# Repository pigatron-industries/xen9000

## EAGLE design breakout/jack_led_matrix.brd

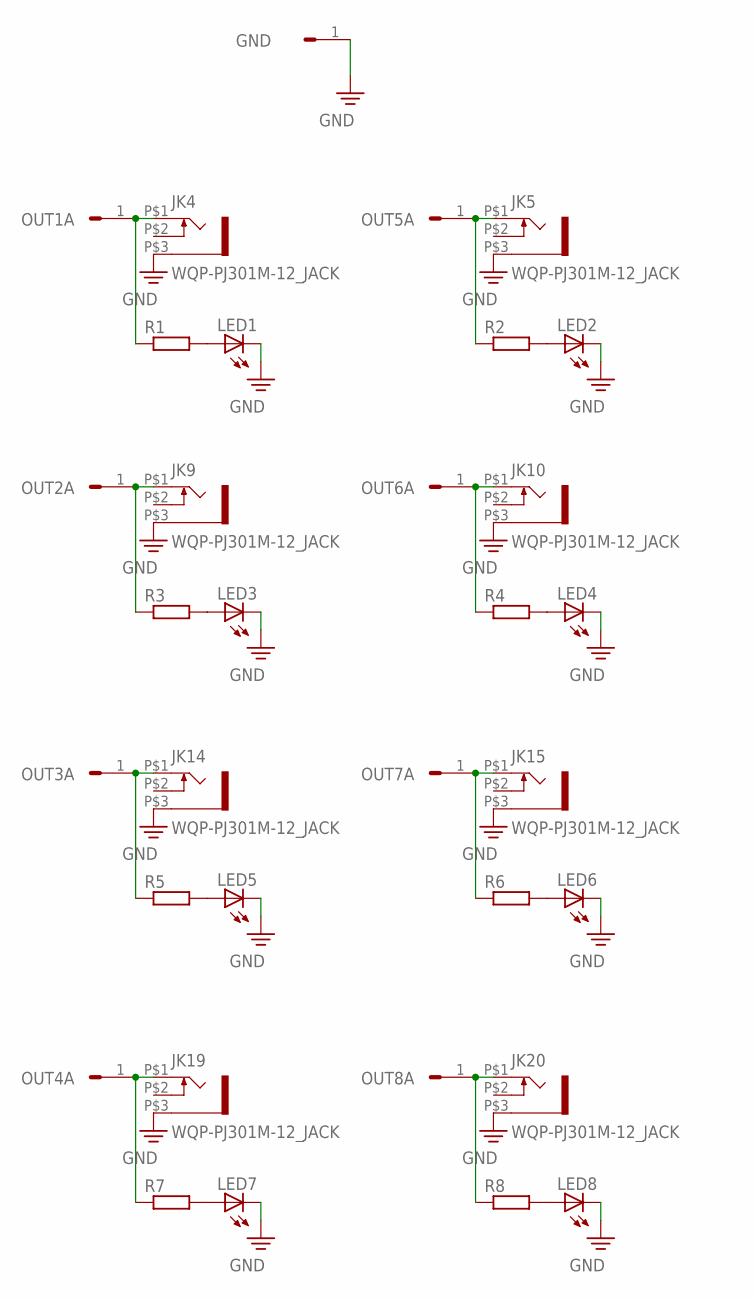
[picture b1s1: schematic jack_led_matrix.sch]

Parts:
GND: HEADER/MALE/01
JK4, JK5, JK9, JK10, JK14, JK15, JK19, JK20: WQP-PJ301M-12_JACK
LED1, LED2, LED3, LED4, LED5, LED6, LED7, LED8: LED3MM
OUT1A, OUT2A, OUT3A, OUT4A, OUT5A, OUT6A, OUT7A, OUT8A: HEADER/MALE/01
R1, R2, R3, R4, R5, R6, R7, R8: RESISTORRESISTOR/UPRIGHT/7.5; RESISTOR/7.5

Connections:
unnamed: JK4.P$1 (2), OUT1A.1, R1.1
unnamed: JK9.P$1 (2), OUT2A.1, R3.1
unnamed: JK14.P$1 (2), OUT3A.1, R5.1
unnamed: JK19.P$1 (2), OUT4A.1, R7.1
unnamed: JK5.P$1 (2), OUT5A.1, R2.1
unnamed: JK10.P$1 (2), OUT6A.1, R4.1
unnamed: JK15.P$1 (2), OUT7A.1, R6.1
unnamed: JK20.P$1 (2), OUT8A.1, R8.1
unnamed: LED1.A, R1.2
unnamed: LED2.A, R2.2
unnamed: LED3.A, R3.2
unnamed: LED4.A, R4.2
unnamed: LED5.A, R5.2
unnamed: LED6.A, R6.2
unnamed: LED7.A, R7.2
unnamed: LED8.A, R8.2
PE: GND.1, JK4.P$3 (1), JK5.P$3 (1), JK9.P$3 (1), JK10.P$3 (1), JK14.P$3 (1), JK15.P$3 (1), JK19.P$3 (1), JK20.P$3 (1), LED1.K (C), LED2.K (C), LED3.K (C), LED4.K (C), LED5.K (C), LED6.K (C), LED7.K (C), LED8.K (C)

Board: 2 copper layers, 33 parts (0 on the bottom side), 17 nets, no tracks yet.

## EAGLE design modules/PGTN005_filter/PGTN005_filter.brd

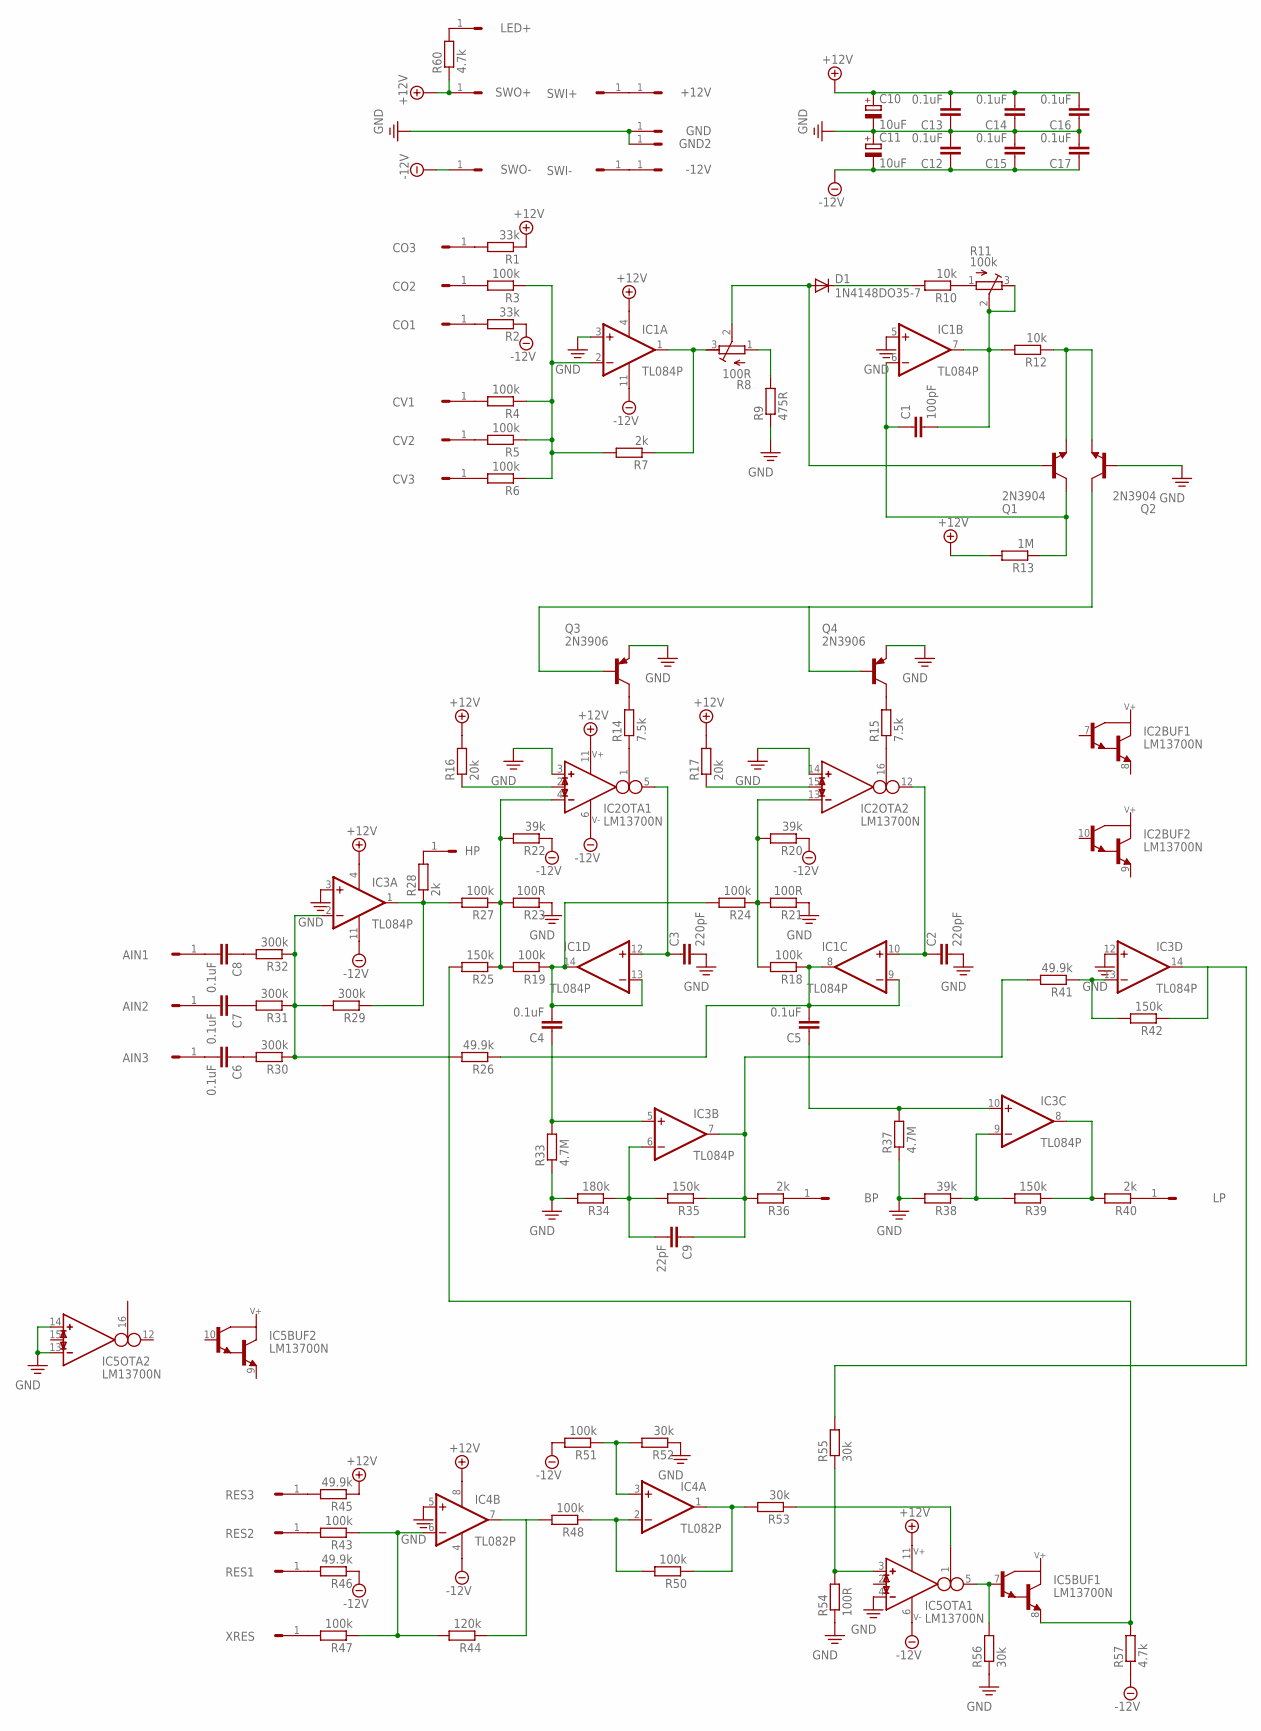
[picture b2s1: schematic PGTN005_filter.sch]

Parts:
+12V: HEADER/MALE/01
-12V: HEADER/MALE/01
AIN1, AIN2, AIN3: HEADER/MALE/01
BP: HEADER/MALE/01
C1: 100pF; CERAMICDISC/5
C2, C3: 220pF; CERAMICDISC/5
C4, C5, C6, C7, C8, C12, C13, C14, C15, C16, C17: 0.1uF; CERAMICDISC/5
C9: 22pF; CERAMICDISC/5
C10, C11: 10uF; E2,5-6
CO1, CO2, CO3: HEADER/MALE/01
CV1, CV2, CV3: HEADER/MALE/01
D1: 1N4148DO35-7; DO35-7
GND, GND2: HEADER/MALE/01
HP: HEADER/MALE/01
IC1, IC3: TL084P; DIL14
IC2, IC5: LM13700N; DIL16
IC4: TL082P; DIL08
LED+: HEADER/MALE/01
LP: HEADER/MALE/01
Q1, Q2: 2N3904; TO92
Q3, Q4: 2N3906; TO92
R1, R2: 33k; RESISTOR/7.5
R3, R4, R5, R6, R18, R19, R24, R27, R43, R47, R48, R50, R51: 100k; RESISTOR/7.5
R7, R28, R36, R40: 2k; RESISTOR/7.5
R8: 100R; TRIMMER/64B
R9: 475R; RESISTOR/7.5
R10, R12: 10k; RESISTOR/7.5
R11: 100k; TRIMMER/64B
R13: 1M; RESISTOR/7.5
R14, R15: 7.5k; RESISTOR/7.5
R16, R17: 20k; RESISTOR/7.5
R20, R22, R38: 39k; RESISTOR/7.5
R21, R23, R54: 100R; RESISTOR/7.5
R25, R35, R39, R42: 150k; RESISTOR/7.5
R26, R41, R45, R46: 49.9k; RESISTOR/7.5
R29, R30, R31, R32: 300k; RESISTOR/7.5
R33, R37: 4.7M; RESISTOR/7.5
R34: 180k; RESISTOR/7.5
R44: 120k; RESISTOR/7.5
R52, R53, R55, R56: 30k; RESISTOR/7.5
R57, R60: 4.7k; RESISTOR/7.5
RES1, RES2, RES3: HEADER/MALE/01
SWI+: HEADER/MALE/01
SWI-: HEADER/MALE/01
SWO+: HEADER/MALE/01
SWO-: HEADER/MALE/01
XRES: HEADER/MALE/01

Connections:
+12V: C10.+, C13.2, C14.2, C16.2, IC1.4 (V+), IC2.11 (V+), IC3.4 (V+), IC4.8 (V+), IC5.11 (V+), R1.1, R13.2, R16.2, R17.2, R45.1, R60.1, SWO+.1
-12V: C11.-, C12.1, C15.1, C17.1, IC1.11 (V-), IC2.6 (V-), IC3.11 (V-), IC4.4 (V-), IC5.6 (V-), R2.1, R20.1, R22.1, R46.1, R51.2, R57.1, SWO-.1
unnamed: CO3.1, R1.2
unnamed: CO1.1, R2.2
unnamed: CO2.1, R3.2
unnamed: IC1.2 (-IN), R3.1, R4.1, R5.1, R6.1, R7.2
unnamed: CV1.1, R4.2
unnamed: CV2.1, R5.2
unnamed: CV3.1, R6.2
unnamed: IC1.1 (OUT), R7.1, R8.3 (A)
unnamed: R8.1 (E), R9.2
unnamed: D1.A, Q1.2 (B), R8.2 (S)
unnamed: D1.C, R10.2
unnamed: R10.1, R11.1 (E)
unnamed: C1.2, IC1.7 (OUT), R11.2 (S), R11.3 (A), R12.2
unnamed: C1.1, IC1.6 (-IN), Q1.1 (C), R13.1
unnamed: Q1.3 (E), Q2.3 (E), R12.1
unnamed: Q2.1 (C), Q3.2 (B), Q4.2 (B)
unnamed: Q3.1 (C), R14.2
unnamed: Q4.1 (C), R15.2
unnamed: IC2.1 (I_BIAS), R14.1
unnamed: IC2.16 (I_BIAS), R15.1
unnamed: IC2.2 (I_DIODE), R16.1
unnamed: IC2.15 (I_DIODE), R17.1
unnamed: C2.1, IC1.10 (+IN), IC2.12 (OUT)
unnamed: C3.1, IC1.12 (+IN), IC2.5 (OUT)
unnamed: C5.2, IC1.8 (OUT), IC1.9 (-IN), R18.1, R26.1
unnamed: C4.2, IC1.13 (-IN), IC1.14 (OUT), R19.1, R24.2
unnamed: IC2.13 (IN_N), R18.2, R20.2, R21.2, R24.1
unnamed: IC2.4 (IN_N), R19.2, R22.2, R23.2, R25.1, R27.1
unnamed: IC3.1 (OUT), R27.2, R28.1, R29.1
unnamed: IC3.2 (-IN), R26.2, R29.2, R30.1, R31.1, R32.1
unnamed: HP.1, R28.2
unnamed: C6.1, R30.2
unnamed: C7.1, R31.2
unnamed: C8.1, R32.2
unnamed: AIN1.1, C8.2
unnamed: AIN2.1, C7.2
unnamed: AIN3.1, C6.2
unnamed: C4.1, IC3.5 (+IN), R33.2
unnamed: C9.2, IC3.6 (-IN), R34.1, R35.2
unnamed: C9.1, IC3.7 (OUT), R35.1, R36.2, R41.2
unnamed: BP.1, R36.1
unnamed: C5.1, IC3.10 (+IN), R37.2
unnamed: R45.2, RES3.1
unnamed: IC3.9 (-IN), R38.1, R39.2
unnamed: IC3.8 (OUT), R39.1, R40.2
unnamed: LP.1, R40.1
unnamed: IC3.13 (-IN), R41.1, R42.2
unnamed: IC3.14 (OUT), R42.1, R55.2
unnamed: IC5.8 (E), R25.2, R57.2
unnamed: IC4.6 (-IN), R43.1, R44.2, R47.1
unnamed: IC4.7 (OUT), R44.1, R48.2
unnamed: R43.2, RES2.1
unnamed: R46.2, RES1.1
unnamed: R47.2, XRES.1
unnamed: IC4.1 (OUT), R50.1, R53.2
unnamed: IC4.2 (-IN), R48.1, R50.2
unnamed: IC4.3 (+IN), R51.1, R52.2
unnamed: IC5.1 (I_BIAS), R53.1
unnamed: IC5.3 (IN_P), R54.2, R55.1
unnamed: IC5.5 (OUT), IC5.7 (B), R56.2
unnamed: +12V.1, SWI+.1
unnamed: -12V.1, SWI-.1
unnamed: LED+.1, R60.2
PE: C2.2, C3.2, C10.-, C11.+, C12.2, C13.1, C14.1, C15.2, C16.1, C17.2, GND.1, GND2.1, IC1.3 (+IN), IC1.5 (+IN), IC2.3 (IN_P), IC2.14 (IN_P), IC3.3 (+IN), IC3.12 (+IN), IC4.5 (+IN), IC5.4 (IN_N), IC5.13 (IN_N), IC5.14 (IN_P), Q2.2 (B), Q3.3 (E), Q4.3 (E), R9.1, R21.1, R23.1, R33.1, R34.2, R37.1, R38.2, R52.1, R54.1, R56.1

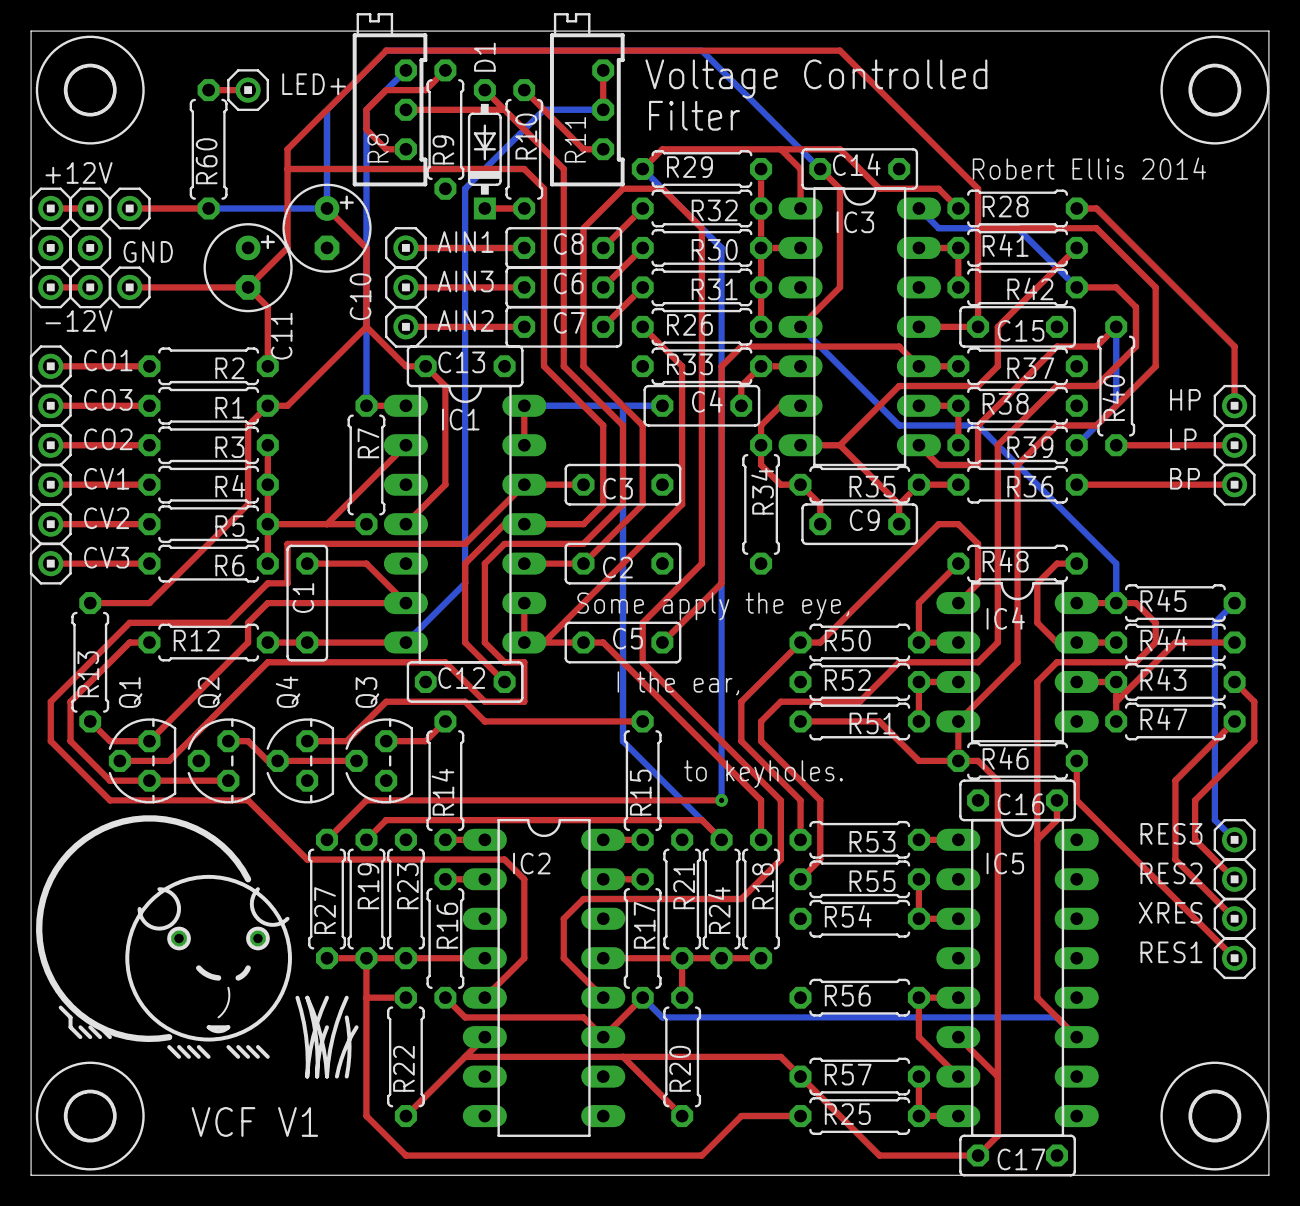
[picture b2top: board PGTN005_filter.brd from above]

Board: 2 copper layers, 79.7 x 73.7 mm, 113 parts (0 on the bottom side), 66 nets.

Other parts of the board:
U$1, U$2, U$3, U$4: STANDOFF/3.0

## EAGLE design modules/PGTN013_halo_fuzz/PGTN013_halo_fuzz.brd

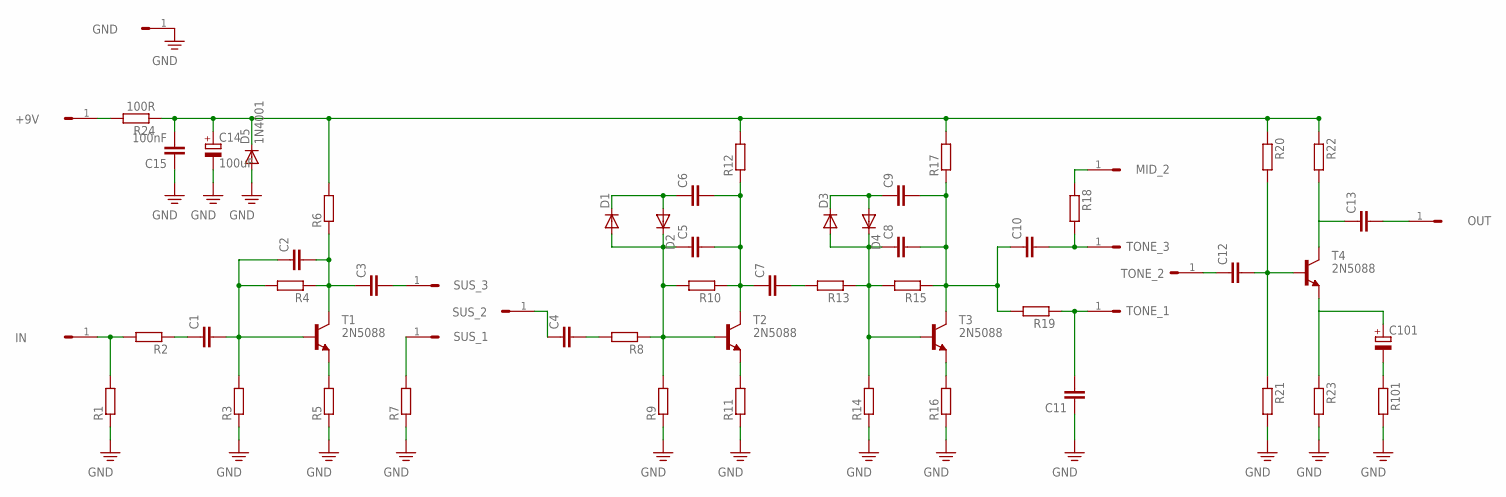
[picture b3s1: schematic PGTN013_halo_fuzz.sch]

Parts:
+9V: HEADER/MALE/01
C1, C2, C3, C4, C5, C6, C7, C8, C9, C10, C11, C12, C13: CAPACITORCERAMICDISC/5; CERAMICDISC/5
C14: 100uF; E3,5-8
C15: 100nF; CERAMICDISC/5
C101: CAPACITOR/POLARIZEDE3.5-8; E3,5-8
D1, D2, D3, D4: 1N4148DO35-7; DO35-7
D5: 1N4001; DO35-7
GND: HEADER/MALE/01
IN: HEADER/MALE/01
MID_2: HEADER/MALE/01
OUT: HEADER/MALE/01
R1, R2, R3, R4, R5, R6, R7, R8, R9, R10, R11, R12, R13, R14, R15, R16, R17, R18, R19, R20, R21, R22, R23, R101: RESISTORRESISTOR/UPRIGHT/7.5; RESISTOR/7.5
R24: 100R; RESISTOR/7.5
SUS_1, SUS_2, SUS_3: HEADER/MALE/01
T1, T2, T3, T4: 2N5088; TO92
TONE_1, TONE_2, TONE_3: HEADER/MALE/01

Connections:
unnamed: IN.1, R1.2, R2.2
unnamed: C1.1, R2.1
unnamed: C1.2, C2.1, R3.2, R4.2, T1.2 (B)
unnamed: C2.2, C3.1, R4.1, R6.1, T1.1 (C)
unnamed: R5.2, T1.3 (E)
unnamed: C3.2, SUS_3.1
unnamed: C14.+, C15.2, D5.C, R6.2, R12.2, R17.2, R20.1, R22.1, R24.1
unnamed: R7.2, SUS_1.1
unnamed: C4.1, SUS_2.1
unnamed: C4.2, R8.2
unnamed: C5.1, D1.A, D2.C, R8.1, R9.2, R10.2, T2.2 (B)
unnamed: C5.2, C6.2, C7.1, R10.1, R12.1, T2.1 (C)
unnamed: R11.2, T2.3 (E)
unnamed: C6.1, D1.C, D2.A
unnamed: C7.2, R13.2
unnamed: C8.1, D3.A, D4.C, R13.1, R14.2, R15.2, T3.2 (B)
unnamed: C10.2, R18.2, TONE_3.1
unnamed: R16.2, T3.3 (E)
unnamed: C9.1, D3.C, D4.A
unnamed: C8.2, C9.2, C10.1, R15.1, R17.1, R19.2, T3.1 (C)
unnamed: C11.2, R19.1, TONE_1.1
unnamed: MID_2.1, R18.1
unnamed: C12.1, TONE_2.1
unnamed: C12.2, R20.2, R21.1, T4.2 (B)
unnamed: C13.1, R22.2, T4.1 (C)
unnamed: C101.+, R23.1, T4.3 (E)
unnamed: C13.2, OUT.1
unnamed: C101.-, R101.1
unnamed: +9V.1, R24.2
PE: C11.1, C14.-, C15.1, D5.A, GND.1, R1.1, R3.1, R5.1, R7.1, R9.1, R11.1, R14.1, R16.1, R21.2, R23.2, R101.2

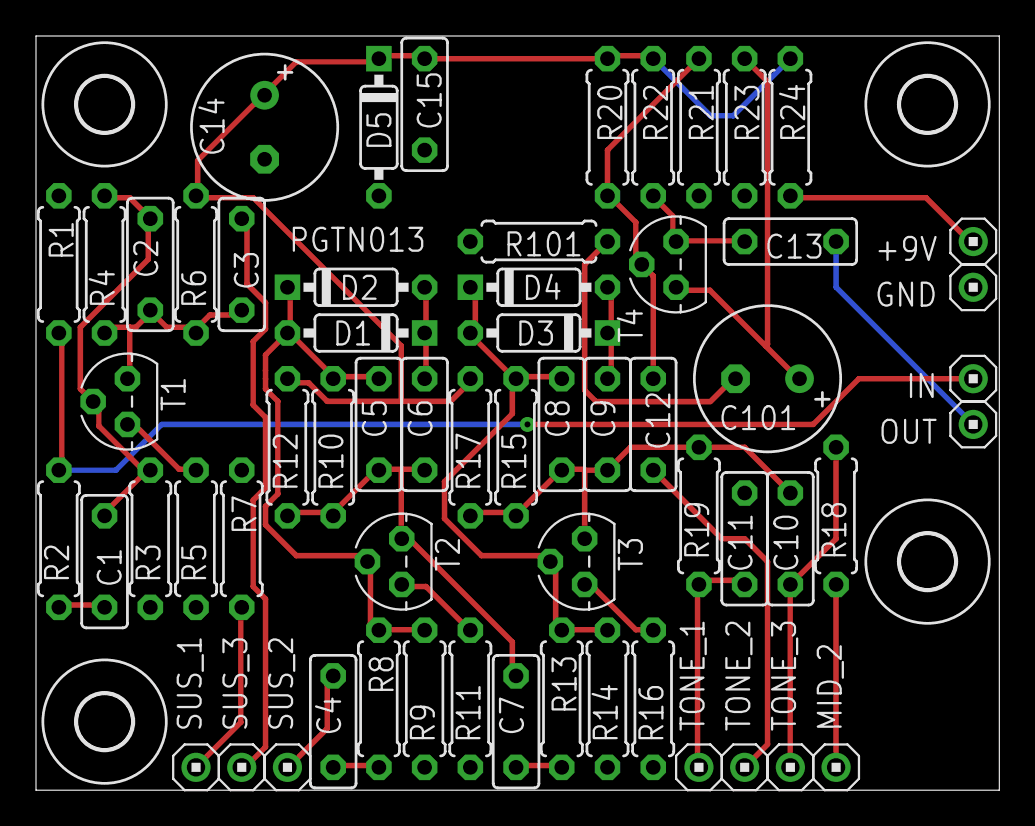
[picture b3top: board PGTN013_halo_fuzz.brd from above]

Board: 2 copper layers, 53.5 x 41.9 mm, 66 parts (1 on the bottom side), 30 nets.

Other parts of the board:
U$1, U$2, U$3, U$4: STANDOFF/3.0
U$5: PIGATRON-LOGO

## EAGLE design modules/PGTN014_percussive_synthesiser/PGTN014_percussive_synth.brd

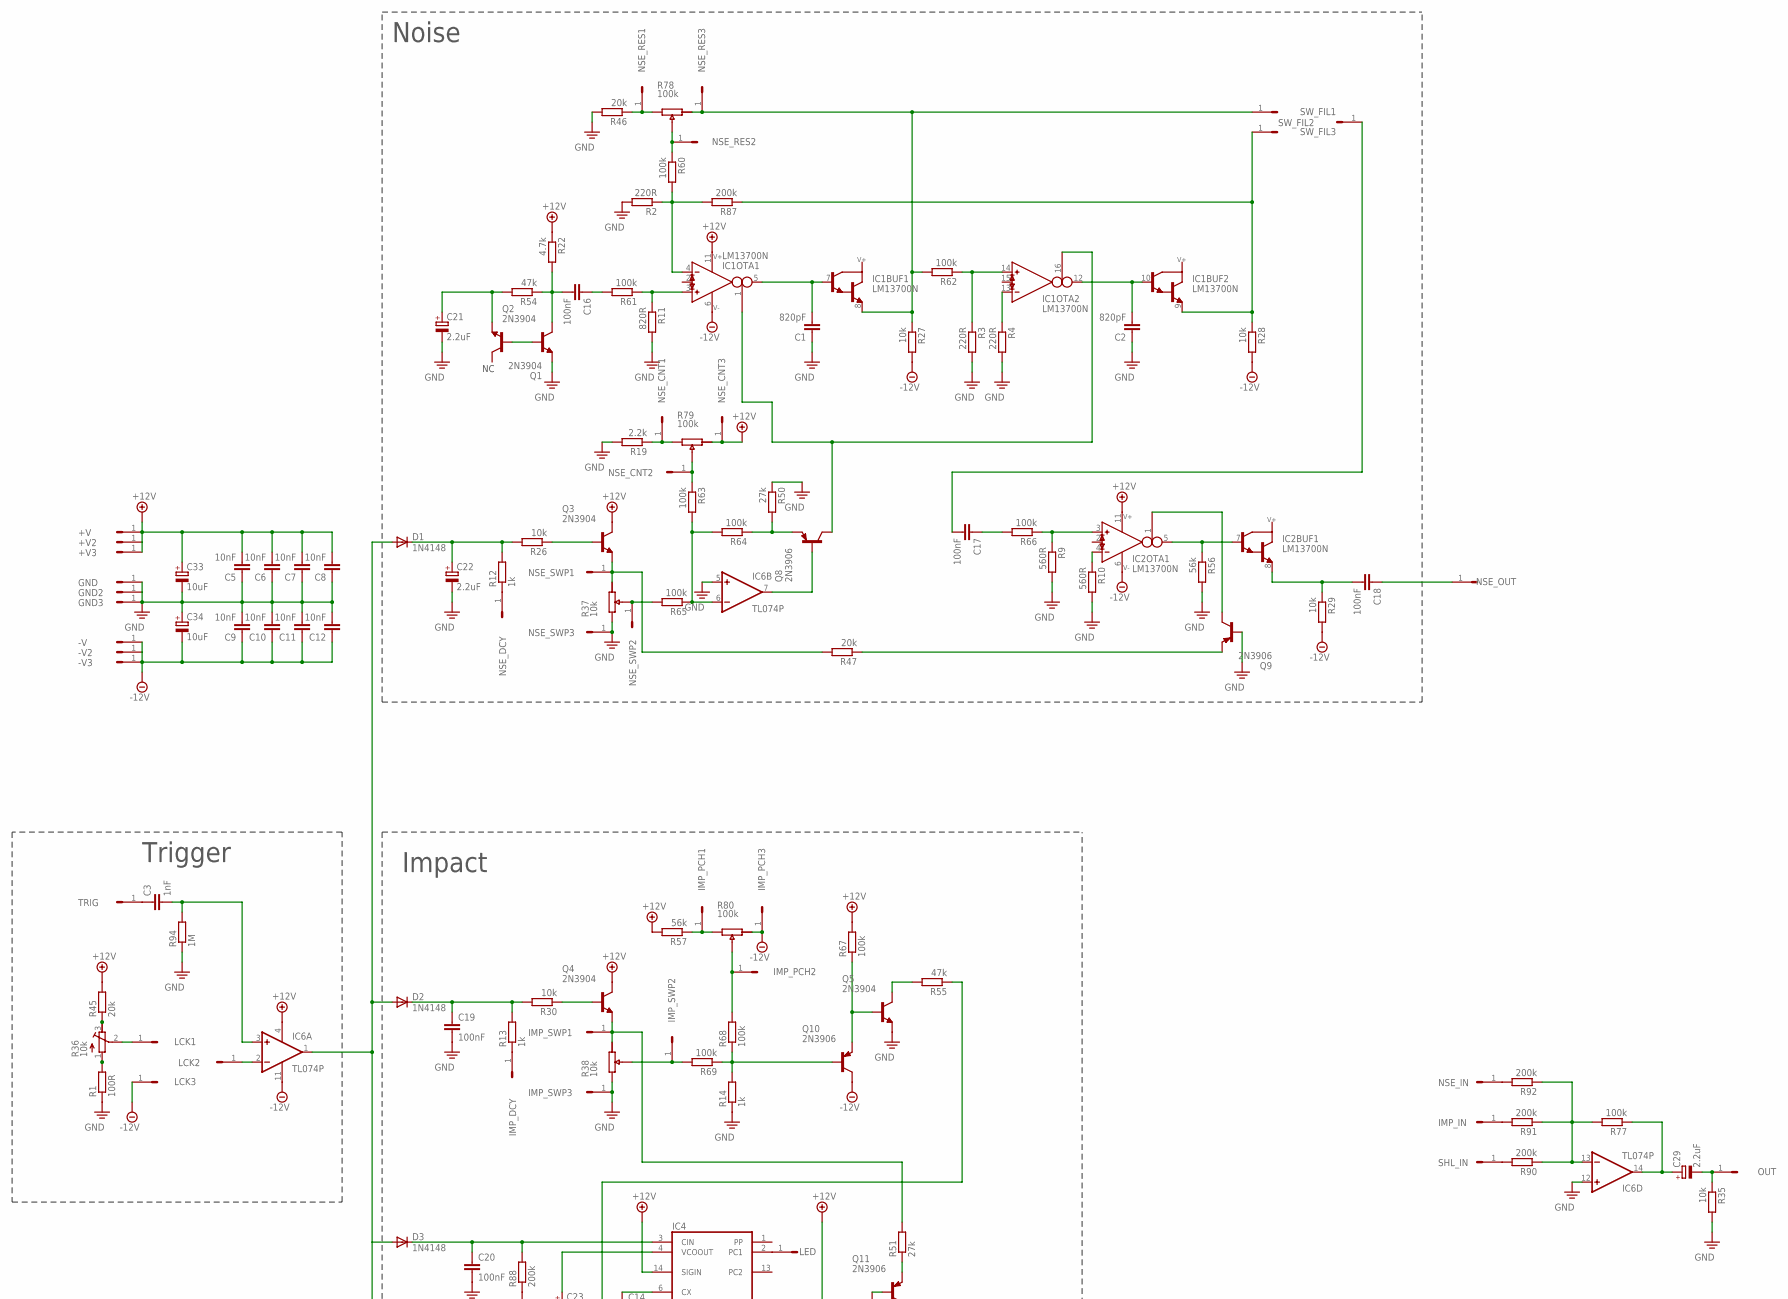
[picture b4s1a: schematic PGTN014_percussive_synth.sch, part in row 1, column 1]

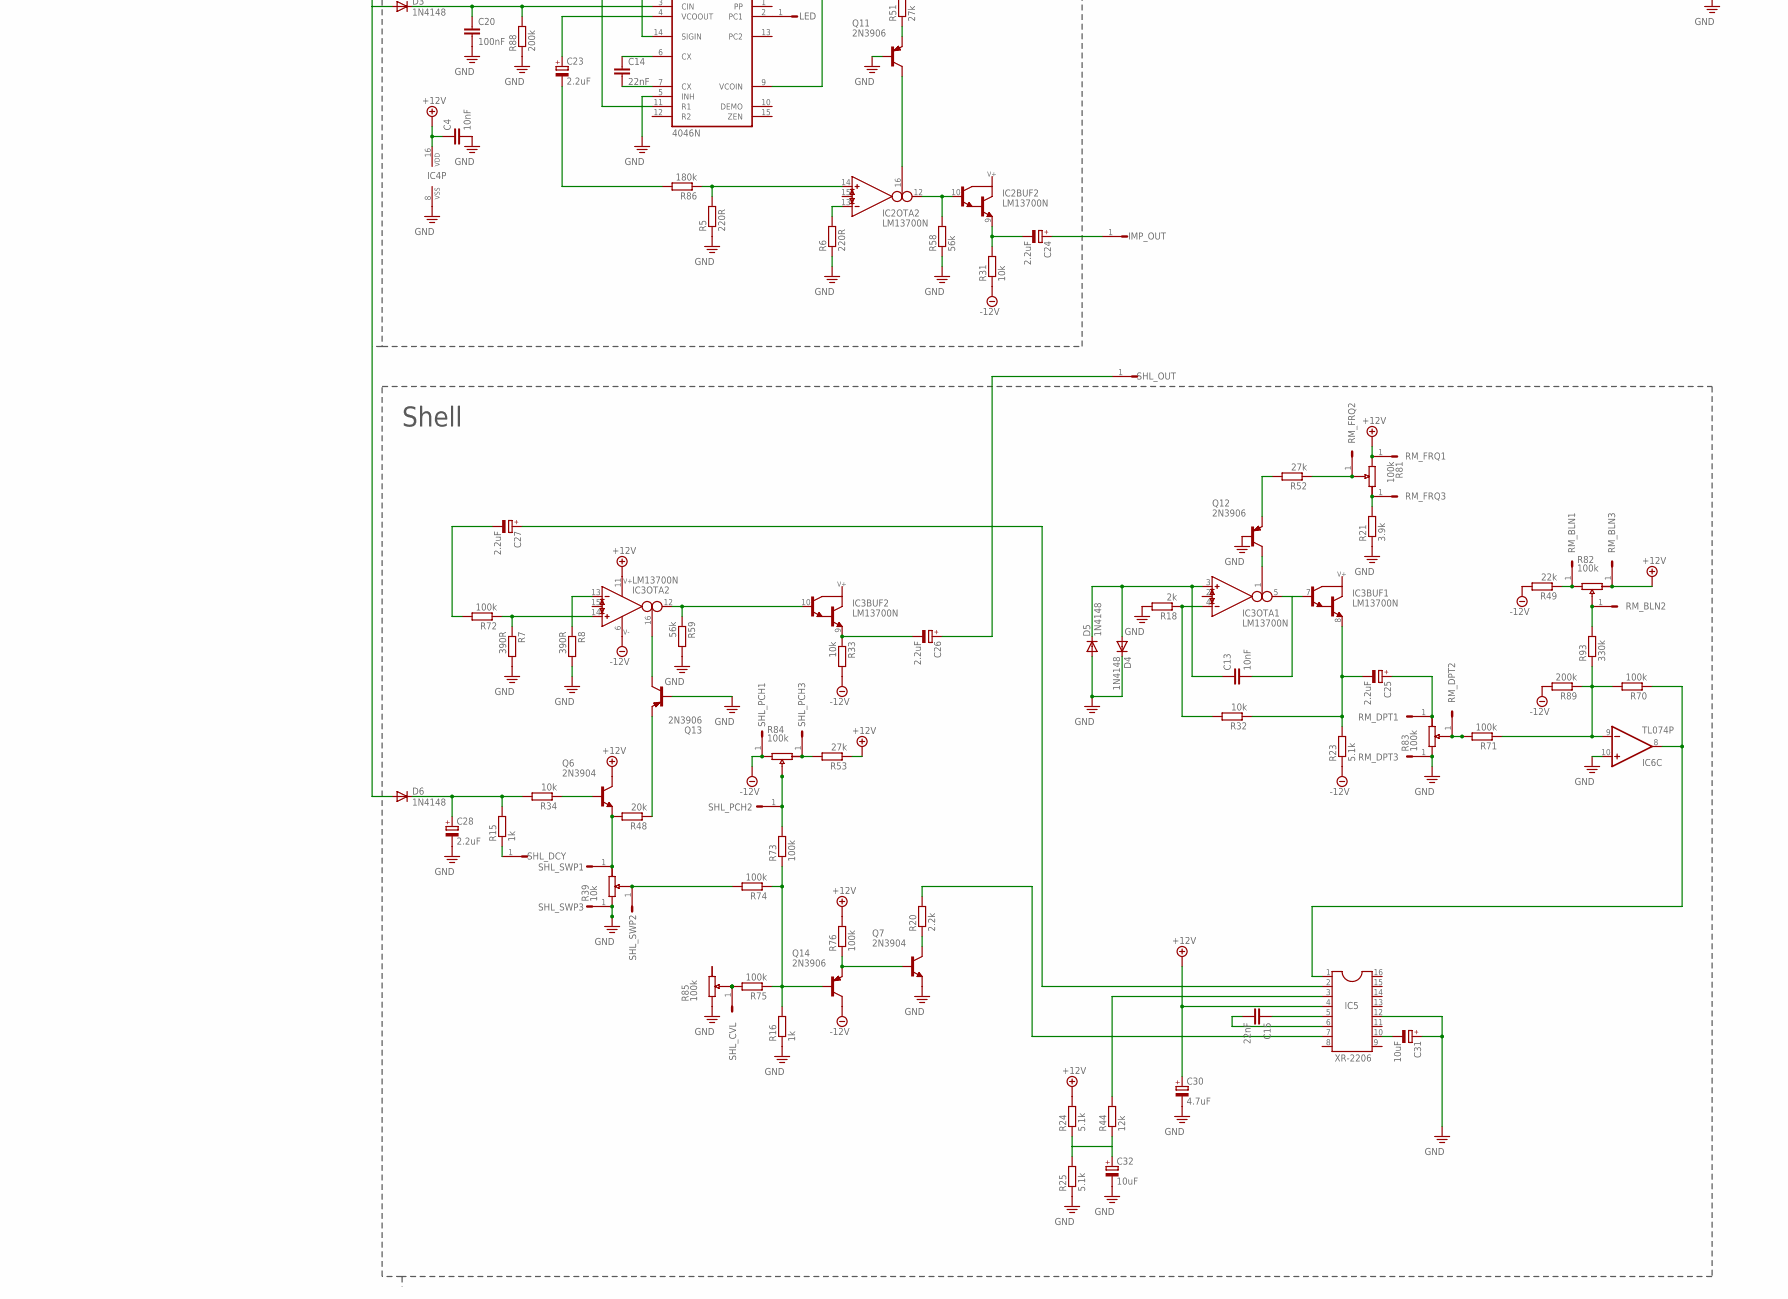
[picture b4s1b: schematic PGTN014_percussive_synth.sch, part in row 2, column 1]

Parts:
+V, +V2, +V3: HEADER/MALE/01
-V, -V2, -V3: HEADER/MALE/01
C1, C2: 820pF; CERAMICDISC/5
C3: 1nF; CERAMICDISC/5
C4, C5, C6, C7, C8, C9, C10, C11, C12, C13: 10nF; CERAMICDISC/5
C14, C15: 22nF; CERAMICDISC/5
C16, C17, C18, C19, C20: 100nF; CERAMICDISC/5
C21, C22, C23, C24, C25, C26, C27, C28, C29: 2.2uF; E2,5-6
C30: 4.7uF; E2,5-6
C31, C32, C33, C34: 10uF; E2,5-6
D1, D2, D3, D4, D5, D6: 1N4148; DO35-7
GND, GND2, GND3: HEADER/MALE/01
IC1, IC2, IC3: LM13700N; DIL16
IC4: 4046N; DIL16
IC5: XR-2206; DIL16
IC6: TL074P; DIL14
IMP_DCY: HEADER/MALE/01
IMP_IN: HEADER/MALE/01
IMP_OUT: HEADER/MALE/01
IMP_PCH1, IMP_PCH2, IMP_PCH3: HEADER/MALE/01
IMP_SWP1, IMP_SWP2, IMP_SWP3: HEADER/MALE/01
LCK1, LCK2, LCK3: HEADER/MALE/01
LED: HEADER/MALE/01
NSE_CNT1, NSE_CNT2, NSE_CNT3: HEADER/MALE/01
NSE_DCY: HEADER/MALE/01
NSE_IN: HEADER/MALE/01
NSE_OUT: HEADER/MALE/01
NSE_RES1, NSE_RES2, NSE_RES3: HEADER/MALE/01
NSE_SWP1, NSE_SWP2, NSE_SWP3: HEADER/MALE/01
OUT: HEADER/MALE/01
Q1, Q2, Q3, Q4, Q5, Q6, Q7: 2N3904; TO92
Q8, Q9, Q10, Q11, Q12, Q13, Q14: 2N3906; TO92
R1: 100R; RESISTOR/7.5
R2, R3, R4, R5, R6: 220R; RESISTOR/7.5
R7, R8: 390R; RESISTOR/7.5
R9, R10: 560R; RESISTOR/7.5
R11: 820R; RESISTOR/7.5
R12, R13, R14, R15, R16: 1k; RESISTOR/7.5
R18: 2k; RESISTOR/7.5
R19, R20: 2.2k; RESISTOR/7.5
R21: 3.9k; RESISTOR/7.5
R22: 4.7k; RESISTOR/7.5
R23, R24, R25: 5.1k; RESISTOR/7.5
R26, R27, R28, R29, R30, R31, R32, R33, R34, R35: 10k; RESISTOR/7.5
R36: 10k; TRIMMER/64B
R44: 12k; RESISTOR/7.5
R45, R46, R47, R48: 20k; RESISTOR/7.5
R49: 22k; RESISTOR/7.5
R50, R51, R52, R53: 27k; RESISTOR/7.5
R54, R55: 47k; RESISTOR/7.5
R56, R57, R58, R59: 56k; RESISTOR/7.5
R60, R61, R62, R63, R64, R65, R66, R67, R68, R69, R70, R71, R72, R73, R74, R75, R76, R77: 100k; RESISTOR/7.5
R86: 180k; RESISTOR/7.5
R87, R88, R89, R90, R91, R92: 200k; RESISTOR/7.5
R93: 330k; RESISTOR/7.5
R94: 1M; RESISTOR/7.5
RM_BLN1, RM_BLN2, RM_BLN3: HEADER/MALE/01
RM_DPT1, RM_DPT2, RM_DPT3: HEADER/MALE/01
RM_FRQ1, RM_FRQ2, RM_FRQ3: HEADER/MALE/01
SHL_CVL: HEADER/MALE/01
SHL_DCY: HEADER/MALE/01
SHL_IN: HEADER/MALE/01
SHL_OUT: HEADER/MALE/01
SHL_PCH1, SHL_PCH2, SHL_PCH3: HEADER/MALE/01
SHL_SWP1, SHL_SWP2, SHL_SWP3: HEADER/MALE/01
SW_FIL1, SW_FIL2, SW_FIL3: HEADER/MALE/01
TRIG: HEADER/MALE/01

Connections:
+12V: +V.1, +V2.1, +V3.1, C4.1, C5.2, C6.2, C7.2, C8.2, C30.+, C33.+, IC1.11 (V+), IC2.11 (V+), IC3.11 (V+), IC4.9 (VCOIN), IC4.14 (SIGIN), IC4.16 (VDD), IC5.4, IC6.4 (V+), NSE_CNT3.1, Q3.1 (C), Q4.1 (C), Q6.1 (C), R22.1, R24.2, R45.2, R53.1, R57.2, R67.2, R76.2, RM_BLN3.1, RM_FRQ1.1
-12V: -V.1, -V2.1, -V3.1, C9.1, C10.1, C11.1, C12.1, C34.-, IC1.6 (V-), IC2.6 (V-), IC3.6 (V-), IC6.11 (V-), IMP_PCH3.1, LCK3.1, Q10.1 (C), Q14.1 (C), R23.1, R27.2, R28.2, R29.2, R31.1, R33.2, R49.2, R89.2, SHL_PCH1.1
GND: C1.1, C2.1, C4.2, C5.1, C6.1, C7.1, C8.1, C9.2, C10.2, C11.2, C12.2, C19.2, C20.2, C21.-, C22.-, C28.-, C30.-, C31.+, C32.-, C33.-, C34.+, D4.C, D5.A, GND.1, GND2.1, GND3.1, IC4.5 (INH), IC4.8 (VSS), IC5.12, IC6.5 (+IN), IC6.10 (+IN), IC6.12 (+IN), IMP_SWP3.1, NSE_SWP3.1, Q2.3 (E), Q5.3 (E), Q7.3 (E), Q9.2 (B), Q11.2 (B), Q12.2 (B), Q13.2 (B), R1.1, R2.2, R3.2, R4.2, R5.1, R6.1, R7.2, R8.2, R9.2, R10.2, R11.2, R14.1, R16.1, R18.2, R19.2, R21.1, R25.1, R35.2, R46.2, R50.1, R56.2, R58.1, R59.2, R88.1, R94.1, RM_DPT3.1, SHL_SWP3.1
unnamed: R36.3 (A), R45.1
unnamed: R1.2, R36.1 (E)
unnamed: LCK1.1, R36.2 (S)
unnamed: IC6.2 (-IN), LCK2.1
unnamed: C3.1, TRIG.1
unnamed: C3.2, IC6.3 (+IN), R94.2
unnamed: D1.A, D2.A, D3.A, D6.A, IC6.1 (OUT)
unnamed: C22.+, D1.C, R12.2, R26.2
unnamed: NSE_DCY.1, R12.1
unnamed: Q3.2 (B), R26.1
unnamed: NSE_SWP1.1, Q3.3 (E), R47.2
unnamed: IC6.6 (-IN), R63.2, R64.2, R65.1
unnamed: NSE_SWP2.1, R65.2
unnamed: IC6.7 (OUT), Q8.2 (B)
unnamed: Q8.3 (E), R50.2, R64.1
unnamed: NSE_CNT2.1, R63.1
unnamed: NSE_CNT1.1, R19.1
unnamed: IC1.1 (I_BIAS), IC1.16 (I_BIAS), Q8.1 (C)
unnamed: C1.2, IC1.5 (OUT), IC1.7 (B)
unnamed: C2.2, IC1.10 (B), IC1.12 (OUT)
unnamed: IC1.14 (IN_P), R3.1, R62.1
unnamed: C17.2, SW_FIL2.1
unnamed: IC1.13 (IN_N), R4.1
unnamed: IC1.9 (E), R28.1, R87.1, SW_FIL3.1
unnamed: IC1.3 (IN_P), R11.1, R61.1
unnamed: C16.1, R61.2
unnamed: C16.2, Q2.1 (C), R22.2, R54.1
unnamed: C21.+, Q1.3 (E), R54.2
unnamed: Q1.2 (B), Q2.2 (B)
unnamed: IC1.4 (IN_N), R2.1, R60.2, R87.2
unnamed: NSE_RES2.1, R60.1
unnamed: NSE_RES1.1, R46.1
unnamed: IC1.8 (E), NSE_RES3.1, R27.1, R62.2, SW_FIL1.1
unnamed: C17.1, R66.2
unnamed: IC2.3 (IN_P), R9.1, R66.1
unnamed: IC2.5 (OUT), IC2.7 (B), R56.1
unnamed: IC2.1 (I_BIAS), Q9.1 (C)
unnamed: Q9.3 (E), R47.1
unnamed: IC2.4 (IN_N), R10.1
unnamed: C18.2, IC2.8 (E), R29.1
unnamed: C18.1, NSE_OUT.1
unnamed: C19.1, D2.C, R13.2, R30.2
unnamed: IMP_DCY.1, R13.1
unnamed: Q4.2 (B), R30.1
unnamed: IMP_SWP1.1, Q4.3 (E), R51.2
unnamed: IMP_SWP2.1, R69.2
unnamed: Q10.2 (B), R14.2, R68.1, R69.1
unnamed: IMP_PCH2.1, R68.2
unnamed: Q5.2 (B), Q10.3 (E), R67.1
unnamed: IMP_PCH1.1, R57.1
unnamed: Q5.1 (C), R55.2
unnamed: IC4.11 (R1), R55.1
unnamed: C20.1, D3.C, IC4.3 (CIN), R88.2
unnamed: IC4.2 (PC1), LED.1
unnamed: C14.1, IC4.6 (CX)
unnamed: C14.2, IC4.7 (CX)
unnamed: C23.+, IC4.4 (VCOOUT)
unnamed: C23.-, R86.2
unnamed: IC2.14 (IN_P), R5.2, R86.1
unnamed: Q11.3 (E), R51.1
unnamed: IC2.16 (I_BIAS), Q11.1 (C)
unnamed: IC2.13 (IN_N), R6.2
unnamed: IC2.10 (B), IC2.12 (OUT), R58.2
unnamed: C24.-, IC2.9 (E), R31.2
unnamed: C24.+, IMP_OUT.1
unnamed: C28.+, D6.C, R15.2, R34.2
unnamed: R15.1, SHL_DCY.1
unnamed: Q6.2 (B), R34.1
unnamed: Q6.3 (E), R48.2, SHL_SWP1.1
unnamed: R74.2, SHL_SWP2.1
unnamed: Q13.3 (E), R48.1
unnamed: Q7.1 (C), R20.1
unnamed: Q14.2 (B), R16.2, R73.1, R74.1, R75.1
unnamed: R73.2, SHL_PCH2.1
unnamed: R75.2, SHL_CVL.1
unnamed: R53.2, SHL_PCH3.1
unnamed: Q7.2 (B), Q14.3 (E), R76.1
unnamed: IC3.16 (I_BIAS), Q13.1 (C)
unnamed: IC3.14 (IN_P), R7.1, R72.1
unnamed: IC3.13 (IN_N), R8.1
unnamed: IC3.10 (B), IC3.12 (OUT), R59.1
unnamed: C26.-, IC3.9 (E), R33.1
unnamed: C27.-, R72.2
unnamed: C13.2, IC3.5 (OUT), IC3.7 (B)
unnamed: IC3.4 (IN_N), R18.1, R32.2
unnamed: C13.1, D4.A, D5.C, IC3.3 (IN_P)
unnamed: C25.-, IC3.8 (E), R23.2, R32.1
unnamed: IC3.1 (I_BIAS), Q12.1 (C)
unnamed: Q12.3 (E), R52.2
unnamed: R52.1, RM_FRQ2.1
unnamed: R21.2, RM_FRQ3.1
unnamed: C25.+, RM_DPT1.1
unnamed: R71.2, RM_DPT2.1
unnamed: IC6.9 (-IN), R70.2, R71.1, R89.1, R93.1
unnamed: IC5.1, IC6.8 (OUT), R70.1
unnamed: R93.2, RM_BLN2.1
unnamed: R49.1, RM_BLN1.1
unnamed: C27.+, IC5.2
unnamed: IC5.7, R20.2
unnamed: C15.1, IC5.5
unnamed: C32.+, R24.1, R25.2, R44.1
unnamed: IC5.3, R44.2
unnamed: C15.2, IC5.6
unnamed: C29.+, IC6.14 (OUT), R77.1
unnamed: C26.+, SHL_OUT.1
unnamed: IC6.13 (-IN), R77.2, R90.1, R91.1, R92.1
unnamed: NSE_IN.1, R92.2
unnamed: IMP_IN.1, R91.2
unnamed: R90.2, SHL_IN.1
unnamed: C29.-, OUT.1, R35.1
unnamed: C31.-, IC5.10

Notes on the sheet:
Trigger
Noise
Impact
Shell
